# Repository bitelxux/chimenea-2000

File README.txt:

# libraries proved to work

Used library      Version Path
ArduinoJson       5.13.5  /home/cnn/Arduino/libraries/ArduinoJson
btlx25                    /home/cnn/MEGA/dev/arduino/btlx25
ESP8266WiFi       1.0     /home/cnn/.arduino15/packages/esp8266/hardware/esp8266/3.1.2/libraries/ESP8266WiFi
ESP8266HTTPClient 1.2     /home/cnn/.arduino15/packages/esp8266/hardware/esp8266/3.1.2/libraries/ESP8266HTTPClient
ArduinoOTA        1.0     /home/cnn/.arduino15/packages/esp8266/hardware/esp8266/3.1.2/libraries/ArduinoOTA
EEPROM            1.0     /home/cnn/.arduino15/packages/esp8266/hardware/esp8266/3.1.2/libraries/EEPROM
NTPClient         3.2.1   /home/cnn/Arduino/libraries/NTPClient
DNSServer         1.1.1   /home/cnn/.arduino15/packages/esp8266/hardware/esp8266/3.1.2/libraries/DNSServer
ESP8266WebServer  1.0     /home/cnn/.arduino15/packages/esp8266/hardware/esp8266/3.1.2/libraries/ESP8266WebServer
WiFiManager       2.0.17  /home/cnn/Arduino/libraries/WiFiManager
ESP8266mDNS       1.2     /home/cnn/.arduino15/packages/esp8266/hardware/esp8266/3.1.2/libraries/ESP8266mDNS

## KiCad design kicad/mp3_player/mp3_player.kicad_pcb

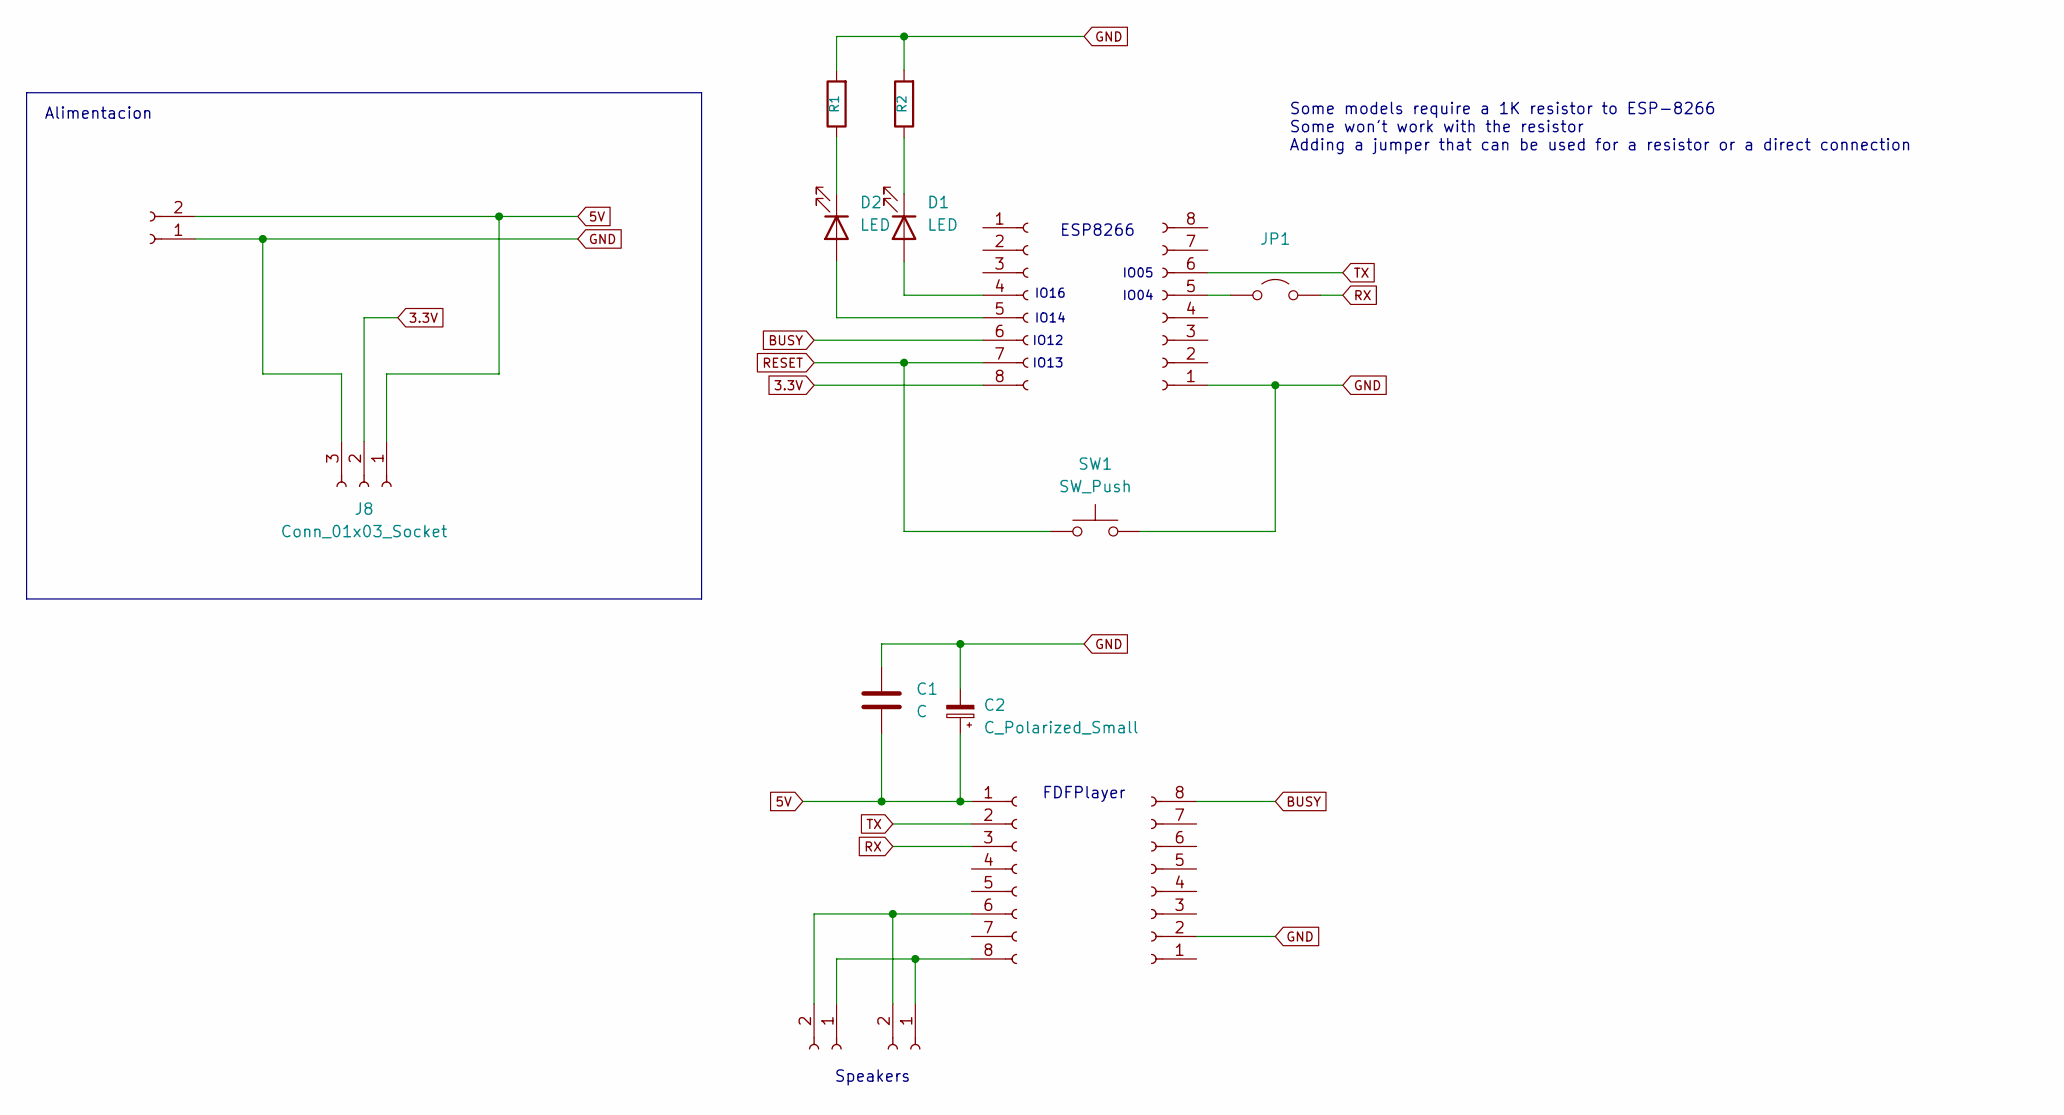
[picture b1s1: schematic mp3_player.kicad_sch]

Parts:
C1: C; C_Disc_D3.0mm_W1.6mm_P2.50mm
C2: C_Polarized_Small; CP_Radial_D7.5mm_P2.50mm
D1, D2: LED; LED_D5.0mm
J1: ESP8266-left; PinSocket_1x08_P2.54mm_Vertical
J2: ESP8266-right; PinSocket_1x08_P2.54mm_Vertical
J3: AC 220; JST_EH_B2B-EH-A_1x02_P2.50mm_Vertical
J4: player-left; PinSocket_1x08_P2.54mm_Vertical
J5: player-right; PinSocket_1x08_P2.54mm_Vertical
J6, J7: Conn_01x02_Socket; JST_EH_B2B-EH-A_1x02_P2.50mm_Vertical
J8: Conn_01x03_Socket; PinSocket_1x03_P2.54mm_Vertical
JP1: Jumper_2_Open; TestPoint_2Pads_Pitch5.08mm_Drill1.3mm
R1, R2: R; R_Axial_DIN0207_L6.3mm_D2.5mm_P7.62mm_Horizontal
SW1: SW_Push; SW_PUSH_6mm_H4.3mm

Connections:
3.3V: J1.8, J8.2
5V: C1.1, C2.1, J3.2, J4.1, J8.1
BUSY: J1.6, J5.8
GND: C1.2, C2.2, J2.1, J3.1, J5.2, J8.3, R1.2, R2.2, SW1.2
unnamed: D1.2 (A), J1.4
unnamed: D1.1 (K), R2.1
unnamed: D2.2 (A), J1.5
unnamed: D2.1 (K), R1.1
unnamed: J2.5, JP1.1 (A)
unnamed: J4.6, J6.2, J7.2
unnamed: J4.8, J6.1, J7.1
RESET: J1.7, SW1.1
RX: J4.3, JP1.2 (B)
TX: J2.6, J4.2

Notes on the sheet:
Alimentacion
Some models require a 1K resistor to ESP-8266 Some won't work with the resistor Adding a jumper that can be used for a resistor or a direct connection
IO14
IO04
ESP8266
FDFPlayer
IO13
IO16
Speakers
IO12
IO05

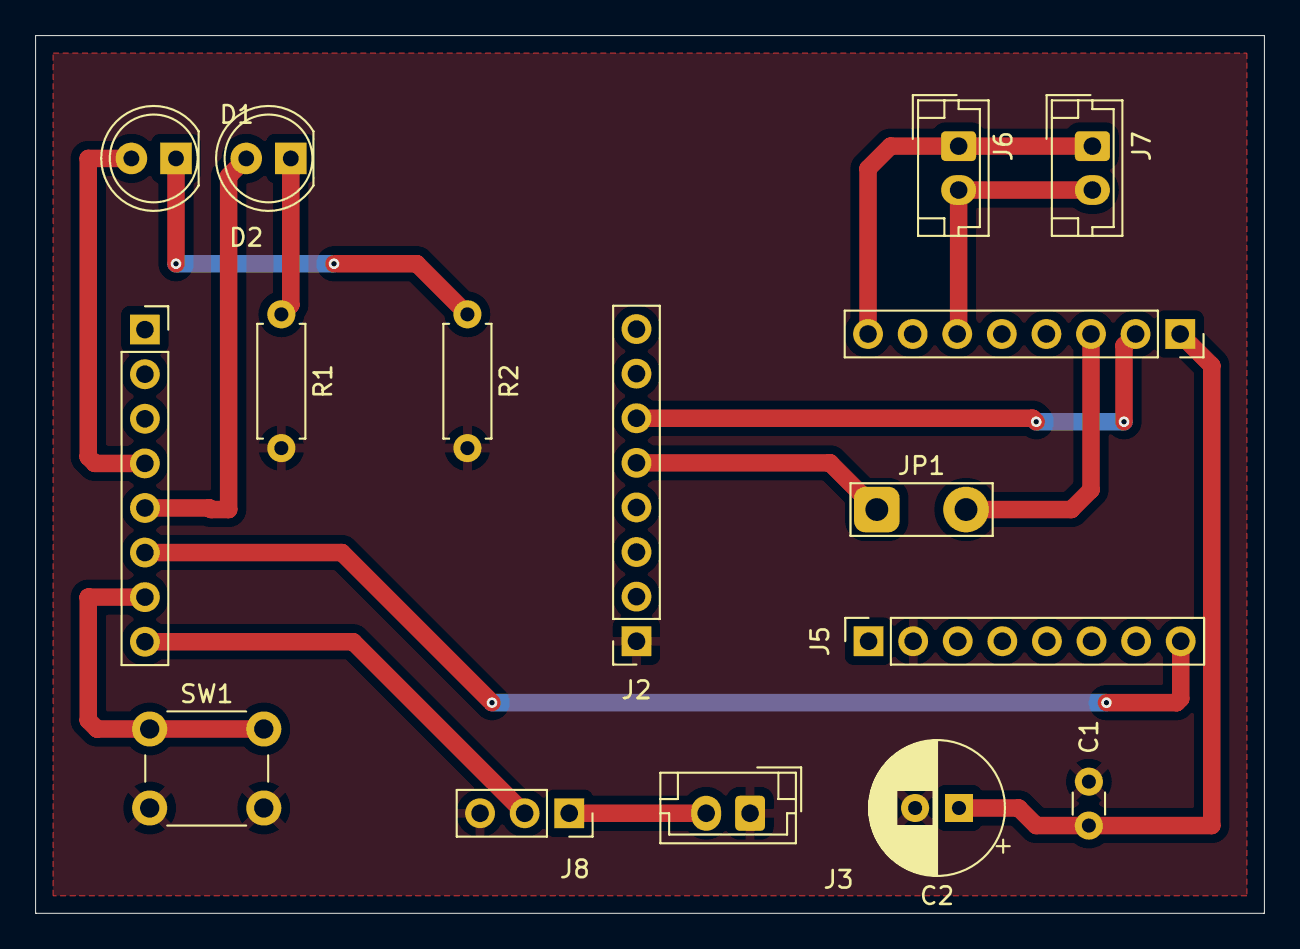
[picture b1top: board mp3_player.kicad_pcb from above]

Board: 2 copper layers, 70.0 x 50.0 mm, 16 parts (0 on the bottom side), 14 nets.

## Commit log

2025-01-25 first html web draft
2025-01-26 change library to btlx25
2025-01-26 config
2025-01-26 failed attempt to use local link to library
2025-01-26 add list of working libraries
2025-01-26 restServer renamed to webServer
2025-01-26 wip webserver
2025-01-26 empty endpoints for mp3 player
2025-01-26 move web stuff to a directory
2025-01-26 move boots management to btlx25
2025-01-27 move millis_to_human to library
2025-01-27 fix buttons behaviour on mobile
2025-01-27 move checkConnection to library
2025-01-28 moving things to web library
2025-01-28 endpoint boardID. Also changing buffers to local scope
2025-01-28 version, uptime and boots
2025-01-28 handle not found
2025-01-28 resetBoots and reboot
2025-01-28 resetEEPROM and cleanup
2025-01-28 simplify log
2025-01-29 fix reboot
2025-01-29 add client IP to log
2025-01-29 placeholders for player actions
2025-01-30 react to FDF playing
2025-01-31 working
2025-01-31 better use of internal libraries
2025-01-31 better use of libraries -moved files
2025-02-01 player class working now
2025-02-01 Player is now derived from DFRobotDFPlayerMini
2025-02-01 Player::trac
2025-02-02 moved to arduino 1.8.5 to be able to use FSLitle to upload files
2025-02-02 index.html in LittleFS now
2025-02-02 IP as environment variable
2025-02-02 trying to upload FS from command line ... still failing
2025-02-02 track number updated in web
2025-02-03 buttons back to their original color on push (android chrome)
2025-02-03 volume indicator
2025-02-03 volume increment 1
2025-02-03 volume color
2025-02-03 comment
2025-02-03 fireplace icon for android
2025-02-04 give serial time to settle. Also started kicad project
2025-02-07 adding reset button
2025-02-07 updated .gitignore
2025-02-08 re-arrange pines
2025-02-08 wifimanager only needs to be started once
2025-02-08 changes around wifi start. Also added controlLed to app
2025-02-08 replacing timers for tickers
2025-02-09 revert global tickers. updateNTP takes too long and board was restarting
2025-02-21 many changes. Main workaround to loop on faulty player
2025-02-21 remove messge
2025-02-21 increase check playing time
2025-02-22 workaround for loop
2025-02-22 explanation about loop workaround
2025-02-23 document double shot issue
2025-02-23 wip board with ground plane
2025-02-23 freecad box model
2025-02-23 failed to fix play double shot
2025-02-23 basic flask log server example
2025-02-23 text
2025-02-23 default track and audio changed
2025-02-26 freecad
